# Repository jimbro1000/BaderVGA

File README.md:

# Terrible VGA #

Inspired by Ben Eater's discrete logic VGA and Leoneq's "bad vga" design,
this project implements a very basic, text only VGA display using just 1 
bit of a 128KB EEPROM data bus and 2KB of SRAM.

## Predictable issues ##

The logic chips used are clocked to near their limit (notably the 12-bit
counters) and struggle to meet the timing requirements of the design. 
Careful selection of components should help to resolve this.

The original designs by Ben and Leoneq were built on breadboard with no
practical ground plane and very little decoupling. This design is a 
dedicated 4-layer PCB with two solid ground planes that should help to 
resolve the problem. As much as possible, all signals are routed on a 
single layer with the "spare" layer used for power delivery.

Timing is not just an issue for the board's clock it is also a problem
for the host. The board clock is decoupled from the host which will,
inevitably, result in read and write conflicts. The host is expected to
be running at 3.147MHz while the video board is running at 20MHz. It
should be viable to gate host r/w operations such that they are blocked
(in the semaphore sense) by the video. If not the only option is to 
restrict write operations to the vertical blank period. The alternative
is to switch to a dual-port arrangement and bypass the problem completely.

## Integration ##
### Inputs ###

Integration with the host requires address bus, data bus, enable/select
and R/!W.

### Outputs ###

Outputs from the board, by default, are just the data bus but this needs
to be extended to include horizontal and vertical sync (TODO)

## Next ##

* Investigate dual-port ram option
* Investigate switch to 25.175MHz for better VGA compliance (can be
driven entirely from the host clock)
* Use latch and 3 bit load counter to reduce contention on databus
* Combine counter with 8 bit shift register (to reduce eeprom size
**and** allow eeprom programming on TL866 without adapters)
* Investigate combining with eeprom based state machine to manage
sync and blank timing

## References ##

Ben Eater VGA <https://eater.net/vga>

Leoneq <https://github.com/Leoneq/iNapGPU>

Dr Matt Regan VGA 
<https://github.com/Turing6502/ZX-Spectrum-No-ULA/blob/main/ZX%20Spectrum%20No%20ULA.pdf>

## License ##

This project is licensed under CC BY-SA 4.0
<https://creativecommons.org/licenses/by-sa/4.0/>

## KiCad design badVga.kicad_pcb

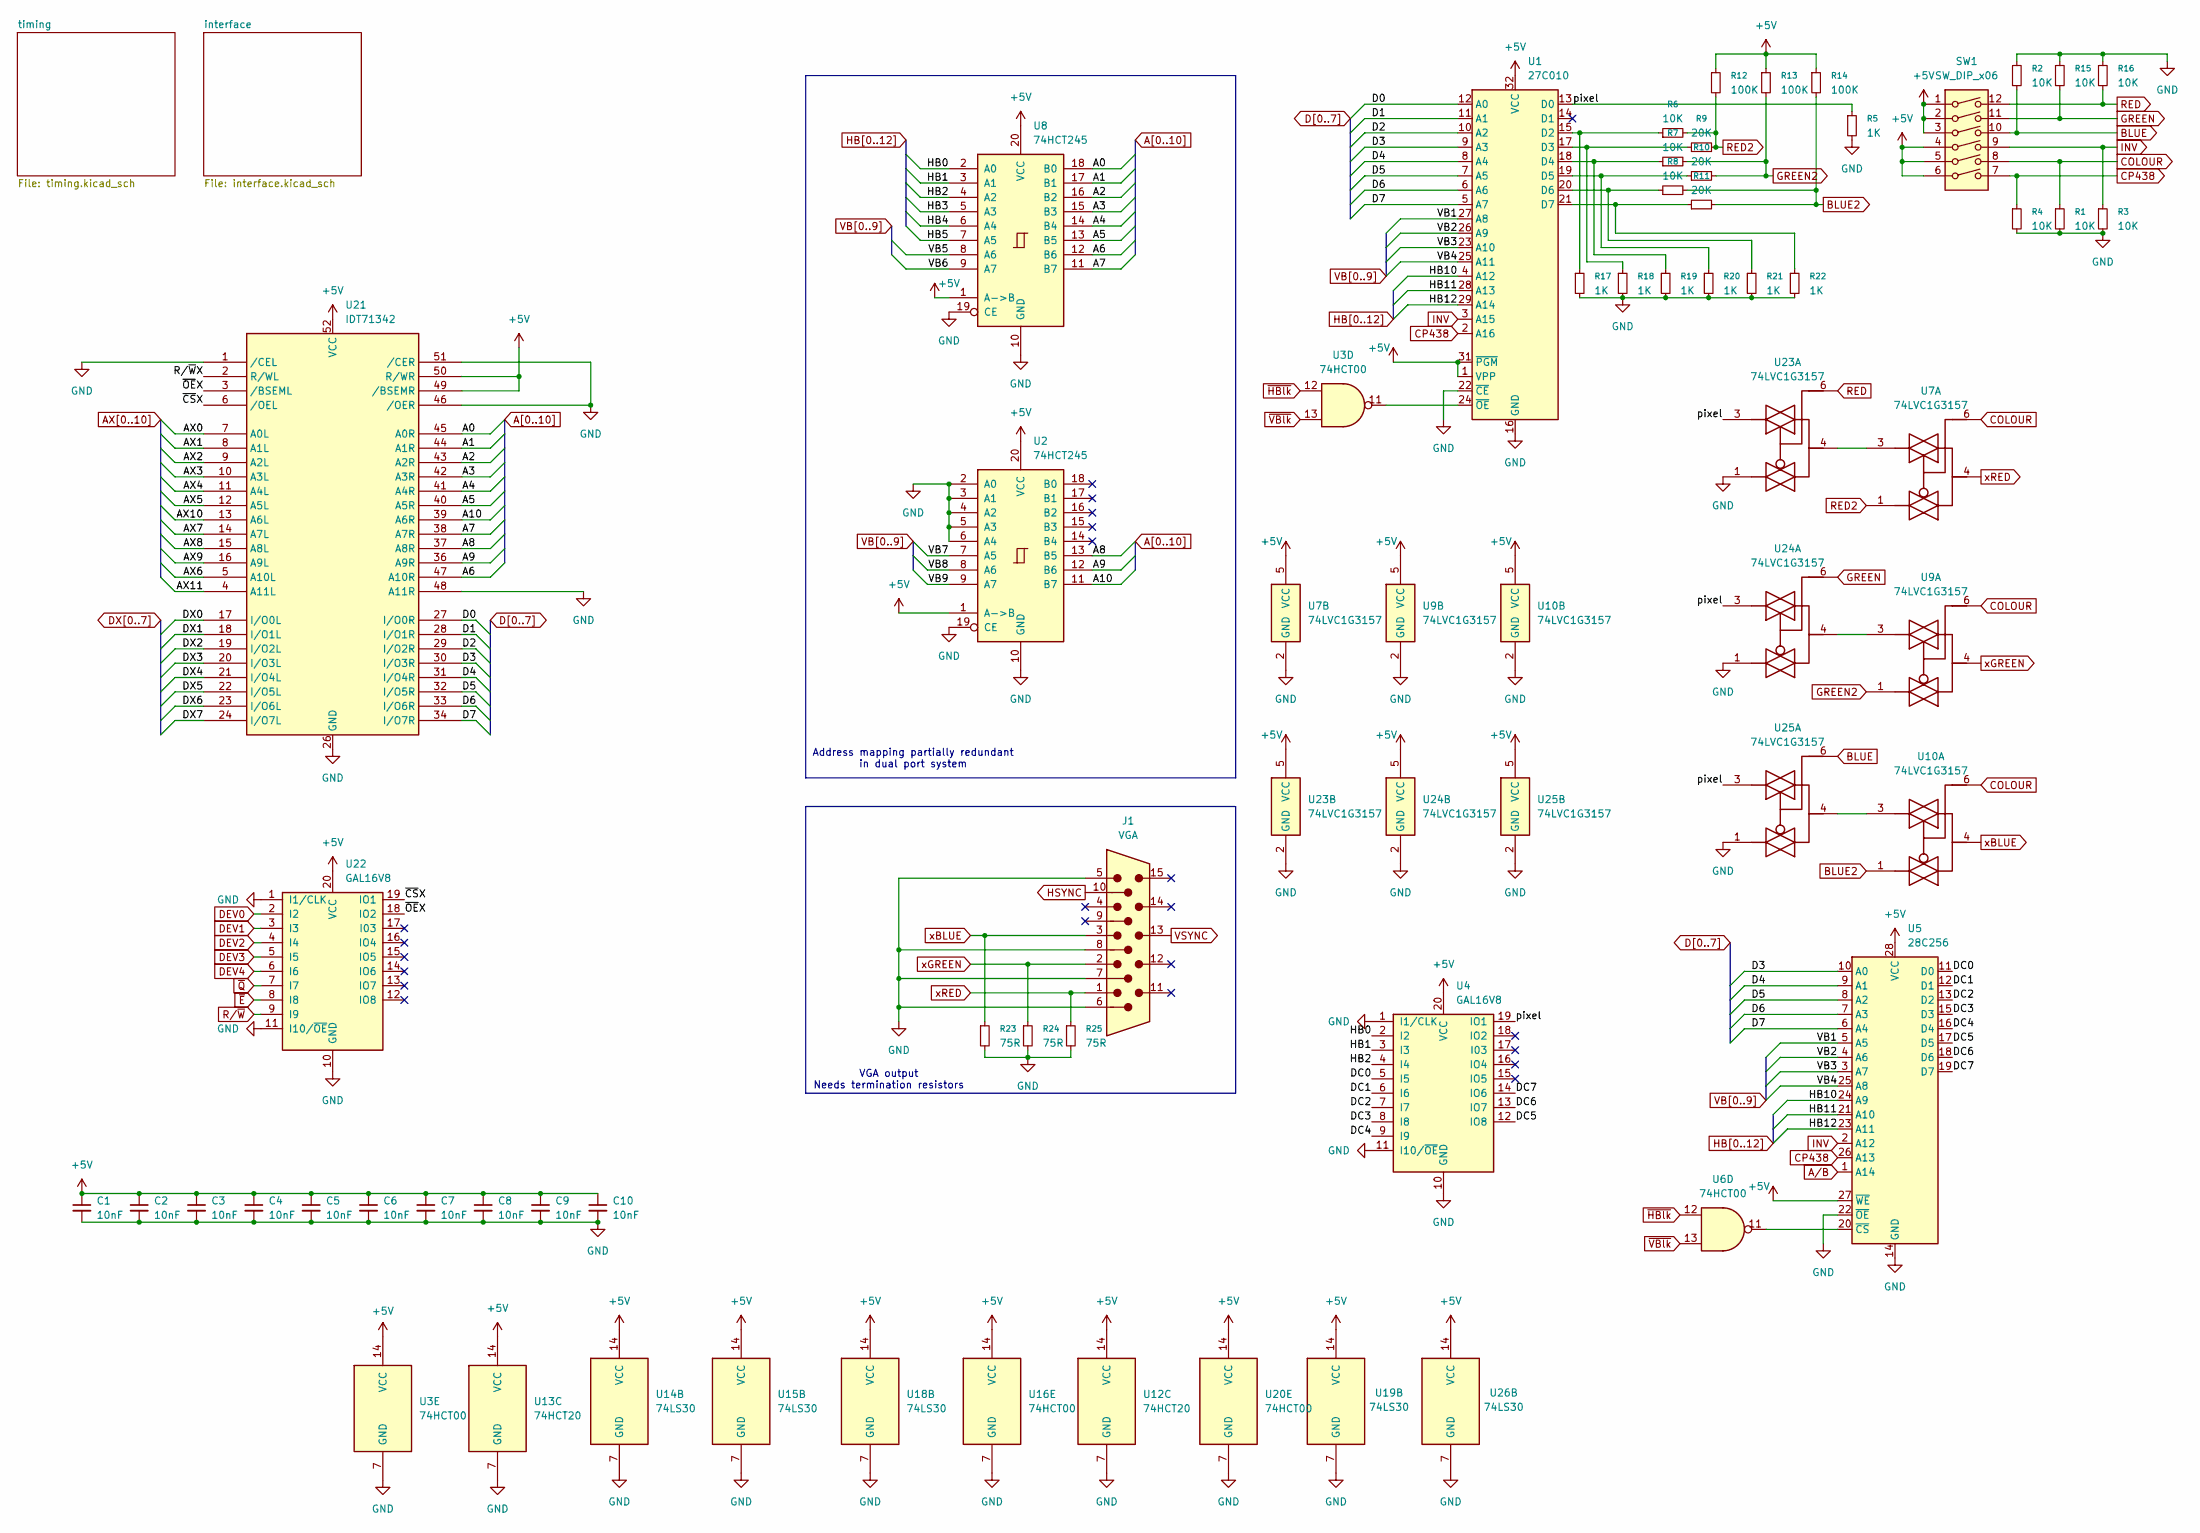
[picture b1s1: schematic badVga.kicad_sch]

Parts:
C1, C2, C3, C4, C5, C6, C7, C8, C9, C10: 10nF; C_0805_2012Metric; LCSC C1710
J1: VGA; DSUB-15-HD_Socket_Horizontal_P2.29x2.54mm_EdgePinOffset8.35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; DigiKey 123-A-HDF15A-KG-TAXB-ND
R1, R2, R3, R4, R15, R16: 10K; R_0603_1608Metric; LCSC C25804
R5, R17, R18, R19, R20, R21, R22: 1K; R_0603_1608Metric; LCSC C21190
R6, R7, R8: 10K; R_0603_1608Metric; LCSC C21190
R9, R10, R11: 20K; R_0603_1608Metric; LCSC C21190
R12, R13, R14: 100K; R_0603_1608Metric; LCSC C21190
R23, R24, R25: 75R; R_0603_1608Metric; LCSC C21190
SW1: SW_DIP_x06; SW_DIP_SPSTx06_Slide_6.7x16.8mm_W7.62mm_P2.54mm_LowProfile
U1: 27C010; DIP-32_W15.24mm
U2, U8: 74HCT245; SOIC-20W_7.5x12.8mm_P1.27mm; LCSC C2675537
U3, U16, U20: 74HCT00; SOIC-14_3.9x8.7mm_P1.27mm; LCSC C609793
U4, U22: GAL16V8; PLCC-20_THT-Socket
U5: 28C256
U6: 74HCT00; SOIC-14_3.9x8.7mm_P1.27mm
U7, U9, U10, U23, U24, U25: 74LVC1G3157; Texas_USON-6_1x1.45mm_P0.5mm_SMD; DigiKey 296-14909-1-ND
U12, U13: 74HCT20; SOIC-14_3.9x8.7mm_P1.27mm; LCSC C556253
U14, U15, U18, U19, U26: 74LS30; SOIC-14_3.9x8.7mm_P1.27mm; LCSC C547583
U21: IDT71342; PLCC-52_THT-Socket

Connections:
+5V: C1.1, C2.1, C3.1, C4.1, C5.1, C6.1, C7.1, C8.1, C9.1, C10.1, R12.1, R13.1, R14.1, SW1.1, SW1.2, SW1.3, SW1.4, SW1.5, SW1.6, U1.1 (VPP), U1.31 (~PGM), U1.32 (VCC), U2.1 (A->B), U2.20 (VCC), U3.14 (VCC), U4.20 (VCC), U5.27 (~WE), U5.28 (VCC), U7.5 (VCC), U8.1 (A->B), U8.20 (VCC), U9.5 (VCC), U10.5 (VCC), U12.14 (VCC), U13.14 (VCC), U14.14 (VCC), U15.14 (VCC), U16.14 (VCC), U18.14 (VCC), U19.14 (VCC), U20.14 (VCC), U21.49 (/BSEMR), U21.50 (R/WR), U21.52 (VCC), U22.20 (VCC), U23.5 (VCC), U24.5 (VCC), U25.5 (VCC), U26.14 (VCC); also elsewhere on the board
/AX11: U21.4 (A11L)
/R/~WX: U21.2 (R/WL)
/pixel: R5.1, U1.13 (D0), U4.19 (IO1), U23.3, U24.3, U25.3
/~CSX: U21.6 (/OEL), U22.19 (IO1)
/~OEX: U21.3 (/BSEML), U22.18 (IO2)
A0: U8.18 (B0), U21.45 (A0R)
A1: U8.17 (B1), U21.44 (A1R)
A2: U8.16 (B2), U21.43 (A2R)
A3: U8.15 (B3), U21.42 (A3R)
A4: U8.14 (B4), U21.41 (A4R)
A5: U8.13 (B5), U21.40 (A5R)
A6: U8.12 (B6), U21.47 (A10R)
A7: U8.11 (B7), U21.38 (A7R)
A8: U2.13 (B5), U21.37 (A8R)
A9: U2.12 (B6), U21.36 (A9R)
A10: U2.11 (B7), U21.39 (A6R)
AX0: U21.7 (A0L); also elsewhere on the board
AX1: U21.8 (A1L); also elsewhere on the board
AX2: U21.9 (A2L); also elsewhere on the board
AX3: U21.10 (A3L); also elsewhere on the board
AX4: U21.11 (A4L); also elsewhere on the board
AX5: U21.12 (A5L); also elsewhere on the board
AX6: U21.5 (A10L); also elsewhere on the board
AX7: U21.14 (A7L); also elsewhere on the board
AX8: U21.15 (A8L); also elsewhere on the board
AX9: U21.16 (A9L); also elsewhere on the board
AX10: U21.13 (A6L); also elsewhere on the board
BLUE: R2.2, SW1.10, U25.6
BLUE2: R8.2, R11.2, R14.2, U10.1
COLOUR: R1.1, SW1.8, U7.6, U9.6, U10.6
CP438: R4.1, SW1.7, U1.2 (A16), U5.26 (A13)
D0: U1.12 (A0), U21.27 (I/O0R)
D1: U1.11 (A1), U21.28 (I/O1R)
D2: U1.10 (A2), U21.29 (I/O2R)
D3: U1.9 (A3), U5.10 (A0), U21.30 (I/O3R)
D4: U1.8 (A4), U5.9 (A1), U21.31 (I/O4R)
D5: U1.7 (A5), U5.8 (A2), U21.32 (I/O5R)
D6: U1.6 (A6), U5.7 (A3), U21.33 (I/O6R)
D7: U1.5 (A7), U5.6 (A4), U21.34 (I/O7R)
DEV0: U22.2 (I2); also elsewhere on the board
DEV1: U22.3 (I3); also elsewhere on the board
DEV2: U22.4 (I4); also elsewhere on the board
DEV3: U22.5 (I5); also elsewhere on the board
DEV4: U22.6 (I6); also elsewhere on the board
DX0: U21.17 (I/O0L); also elsewhere on the board
DX1: U21.18 (I/O1L); also elsewhere on the board
DX2: U21.19 (I/O2L); also elsewhere on the board
DX3: U21.20 (I/O3L); also elsewhere on the board
DX4: U21.21 (I/O4L); also elsewhere on the board
DX5: U21.22 (I/O5L); also elsewhere on the board
DX6: U21.23 (I/O6L); also elsewhere on the board
DX7: U21.24 (I/O7L); also elsewhere on the board
GND: C1.2, C2.2, C3.2, C4.2, C5.2, C6.2, C7.2, C8.2, C9.2, C10.2, J1.5, J1.6, J1.7, J1.8, R1.2, R2.1, R3.2, R4.2, R5.2, R15.1, R16.1, R17.2, R18.2, R19.2, R20.2, R21.2, R22.2, R23.2, R24.2, R25.2, U1.16 (GND), U1.22 (~CE), U2.2 (A0), U2.3 (A1), U2.4 (A2), U2.5 (A3), U2.6 (A4), U2.10 (GND), U2.19 (CE), U3.7 (GND), U4.1 (I1/CLK), U4.10 (GND), U4.11 (I10/~OE), U5.14 (GND), U5.22 (~OE), U7.2 (GND), U8.10 (GND), U8.19 (CE), U9.2 (GND), U10.2 (GND), U12.7 (GND), U13.7 (GND), U14.7 (GND), U15.7 (GND), U16.7 (GND), U18.7 (GND), U19.7 (GND), U20.7 (GND), U21.1 (/CEL), U21.26 (GND), U21.46 (/OER), U21.48 (A11R), U21.51 (/CER), U22.1 (I1/CLK), U22.10 (GND), U22.11 (I10/~OE), U23.1, U23.2 (GND), U24.1, U24.2 (GND), U25.1, U25.2 (GND), U26.7 (GND); also elsewhere on the board
GREEN: R15.2, SW1.11, U24.6
GREEN2: R7.2, R10.2, R13.2, U9.1
HB0: U4.2 (I2), U8.2 (A0); also elsewhere on the board
HB1: U4.3 (I3), U8.3 (A1); also elsewhere on the board
HB2: U4.4 (I4), U8.4 (A2); also elsewhere on the board
HB3: U8.5 (A3); also elsewhere on the board
HB4: U8.6 (A4); also elsewhere on the board
HB5: U8.7 (A5); also elsewhere on the board
HB10: U1.4 (A12), U5.24 (A9); also elsewhere on the board
HB11: U1.28 (A13), U5.21 (A10); also elsewhere on the board
HB12: U1.29 (A14), U5.23 (A11); also elsewhere on the board
HSYNC: J1.10; also elsewhere on the board
INV: R3.1, SW1.9, U1.3 (A15), U5.2 (A12)
unnamed: R6.1, R17.1, U1.15 (D2)
unnamed: R9.1, R18.1, U1.17 (D3)
unnamed: R7.1, R19.1, U1.18 (D4)
unnamed: R10.1, R20.1, U1.19 (D5)
unnamed: R8.1, R21.1, U1.20 (D6)
unnamed: R11.1, R22.1, U1.21 (D7)
unnamed: U1.24 (~OE), U3.11
unnamed: U4.5 (I5), U5.11 (D0)
unnamed: U4.6 (I6), U5.12 (D1)
unnamed: U4.7 (I7), U5.13 (D2)
unnamed: U4.8 (I8), U5.15 (D3)
unnamed: U4.9 (I9), U5.16 (D4)
unnamed: U4.12 (IO8), U5.17 (D5)
unnamed: U4.13 (IO7), U5.18 (D6)
unnamed: U4.14 (IO6), U5.19 (D7)
unnamed: U5.20 (~CS), U6.11
unnamed: U10.3, U25.4
unnamed: U7.3, U23.4
unnamed: U9.3, U24.4
RED: R16.2, SW1.12, U23.6
RED2: R6.2, R9.2, R12.2, U7.1
R/~W: U22.9 (I9); also elsewhere on the board
VB1: U1.27 (A8), U5.5 (A5); also elsewhere on the board
VB2: U1.26 (A9), U5.4 (A6); also elsewhere on the board
VB3: U1.23 (A10), U5.3 (A7); also elsewhere on the board
VB4: U1.25 (A11), U5.25 (A8); also elsewhere on the board
VB5: U8.8 (A6); also elsewhere on the board
VB6: U8.9 (A7); also elsewhere on the board
VB7: U2.7 (A5); also elsewhere on the board
VB8: U2.8 (A6); also elsewhere on the board
VB9: U2.9 (A7); also elsewhere on the board
VSYNC: J1.13; also elsewhere on the board
xBLUE: J1.3, R23.1, U10.4
xGREEN: J1.2, R24.1, U9.4
xRED: J1.1, R25.1, U7.4
~E: U22.8 (I8); also elsewhere on the board
~HBlk: U3.12, U6.12; also elsewhere on the board
~Q: U22.7 (I7); also elsewhere on the board
~VBlk: U3.13, U6.13; also elsewhere on the board

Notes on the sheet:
Address mapping partially redundant in dual port system
VGA output Needs termination resistors

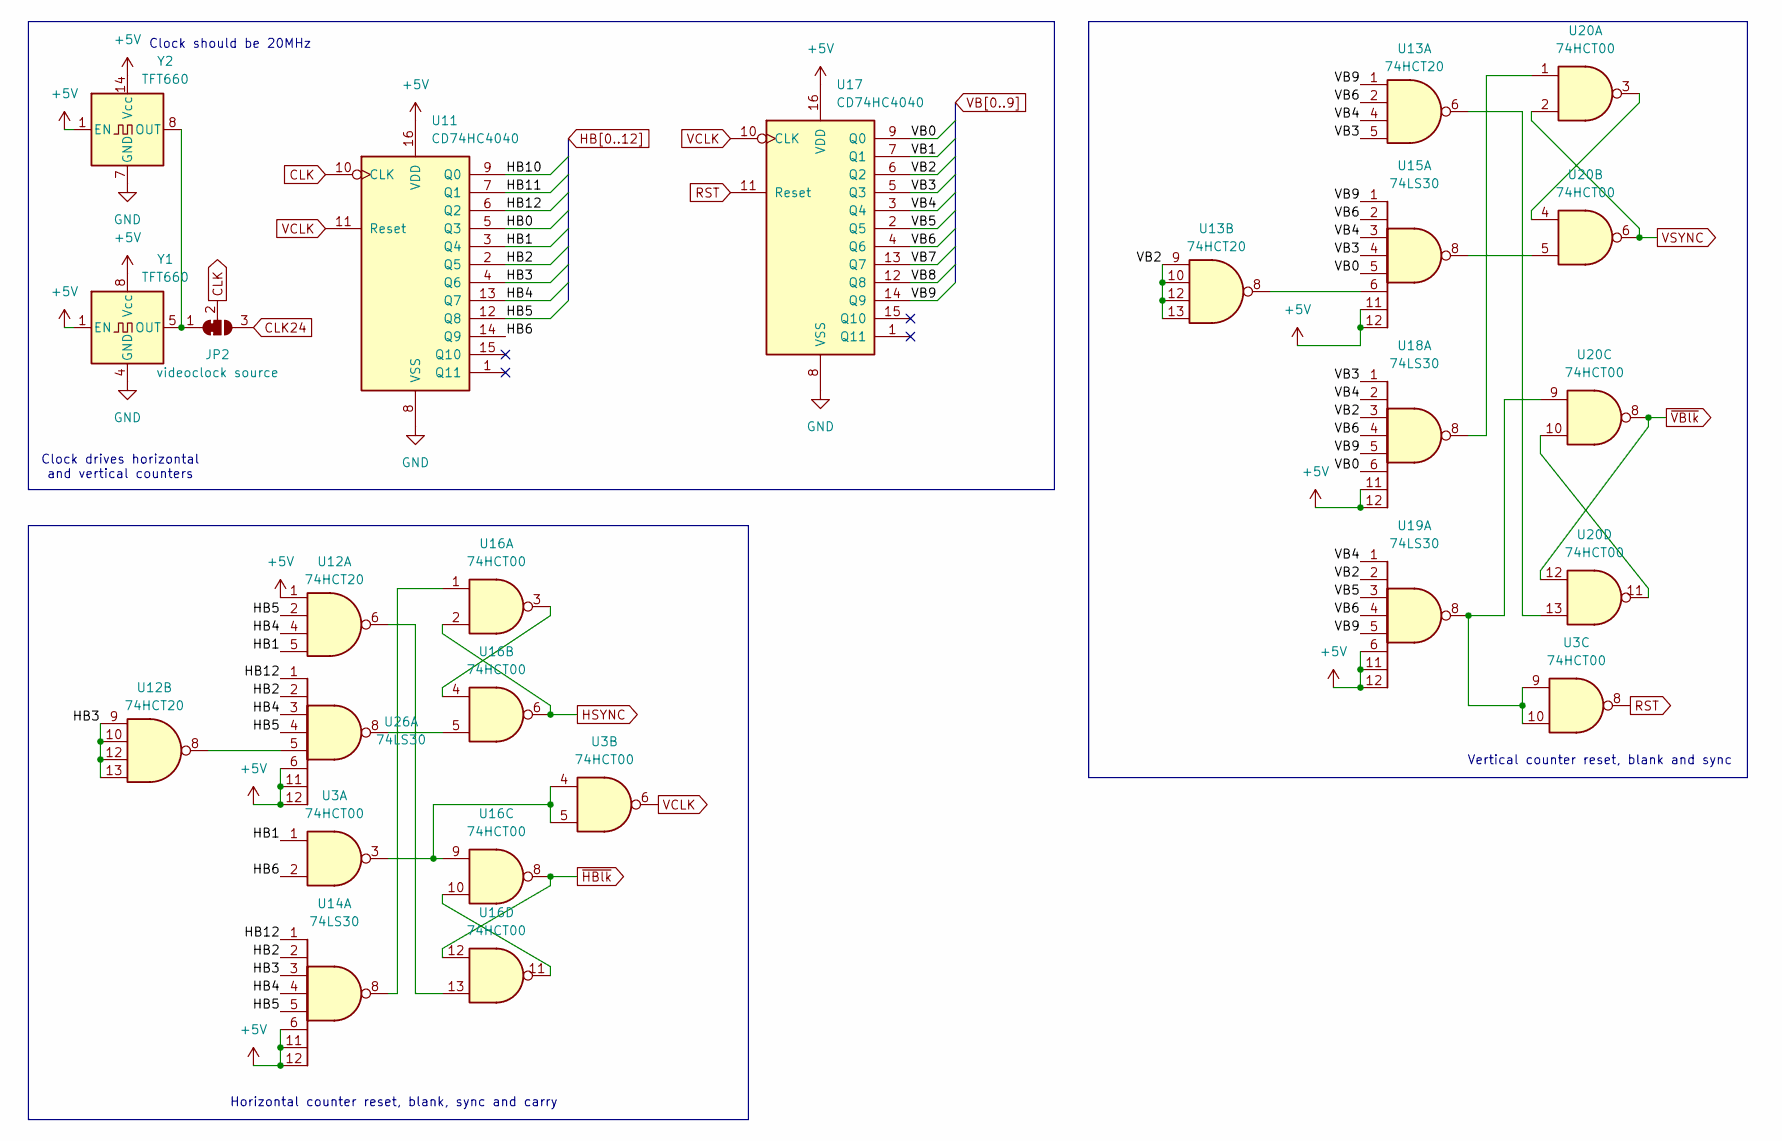
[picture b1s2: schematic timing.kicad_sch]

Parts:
JP2: videoclock source; SolderJumper-3_P1.3mm_Bridged12_Pad1.0x1.5mm
U3, U16, U20: 74HCT00; SOIC-14_3.9x8.7mm_P1.27mm; LCSC C609793
U11, U17: CD74HC4040; SOIC-16_3.9x9.9mm_P1.27mm; LCSC C2865249
U12, U13: 74HCT20; SOIC-14_3.9x8.7mm_P1.27mm; LCSC C556253
U14, U15, U18, U19, U26: 74LS30; SOIC-14_3.9x8.7mm_P1.27mm; LCSC C547583
Y1: TFT660; Oscillator_DIP-8
Y2: TFT660; Oscillator_DIP-14

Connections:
+5V: U11.16 (VDD), U12.1, U14.6, U14.11, U14.12, U15.11, U15.12, U17.16 (VDD), U18.11, U18.12, U19.6, U19.11, U19.12, U26.6, U26.11, U26.12, Y1.1 (EN), Y1.8 (Vcc), Y2.1 (EN), Y2.14 (Vcc); also elsewhere on the board
CLK: JP2.2 (C), U11.10 (CLK)
CLK24: JP2.3 (B); also elsewhere on the board
GND: U11.8 (VSS), U17.8 (VSS), Y1.4 (GND), Y2.7 (GND); also elsewhere on the board
HB0: U11.5 (Q3); also elsewhere on the board
HB1: U3.1, U11.3 (Q4), U12.5; also elsewhere on the board
HB2: U11.2 (Q5), U14.2, U26.2; also elsewhere on the board
HB3: U11.4 (Q6), U12.9, U12.10, U12.12, U12.13, U14.3; also elsewhere on the board
HB4: U11.13 (Q7), U12.4, U14.4, U26.3; also elsewhere on the board
HB5: U11.12 (Q8), U12.2, U14.5, U26.4; also elsewhere on the board
HB6: U3.2, U11.14 (Q9)
HB10: U11.9 (Q0); also elsewhere on the board
HB11: U11.7 (Q1); also elsewhere on the board
HB12: U11.6 (Q2), U14.1, U26.1; also elsewhere on the board
HSYNC: U16.2, U16.6; also elsewhere on the board
unnamed: JP2.1 (A), Y1.5 (OUT), Y2.8 (OUT)
unnamed: U12.6, U16.13
unnamed: U12.8, U26.5
unnamed: U13.6, U20.13
unnamed: U13.8, U15.6
unnamed: U14.8, U16.1
unnamed: U15.8, U20.5
unnamed: U16.3, U16.4
unnamed: U16.5, U26.8
unnamed: U3.3, U3.4, U3.5, U16.9
unnamed: U16.10, U16.11
unnamed: U18.8, U20.1
unnamed: U3.9, U3.10, U19.8, U20.9
unnamed: U20.3, U20.4
unnamed: U20.10, U20.11
RST: U3.8, U17.11 (Reset)
VB0: U15.5, U17.9 (Q0), U18.6
VB1: U17.7 (Q1); also elsewhere on the board
VB2: U13.9, U13.10, U13.12, U13.13, U17.6 (Q2), U18.3, U19.2; also elsewhere on the board
VB3: U13.5, U15.4, U17.5 (Q3), U18.1; also elsewhere on the board
VB4: U13.4, U15.3, U17.3 (Q4), U18.2, U19.1; also elsewhere on the board
VB5: U17.2 (Q5), U19.3; also elsewhere on the board
VB6: U13.2, U15.2, U17.4 (Q6), U18.4, U19.4; also elsewhere on the board
VB7: U17.13 (Q7); also elsewhere on the board
VB8: U17.12 (Q8); also elsewhere on the board
VB9: U13.1, U15.1, U17.14 (Q9), U18.5, U19.5; also elsewhere on the board
VCLK: U3.6, U11.11 (Reset), U17.10 (CLK)
VSYNC: U20.2, U20.6; also elsewhere on the board
~HBlk: U16.8, U16.12; also elsewhere on the board
~VBlk: U20.8, U20.12; also elsewhere on the board

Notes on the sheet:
Clock should be 20MHz
Vertical counter reset, blank and sync
Clock drives horizontal and vertical counters
Horizontal counter reset, blank, sync and carry

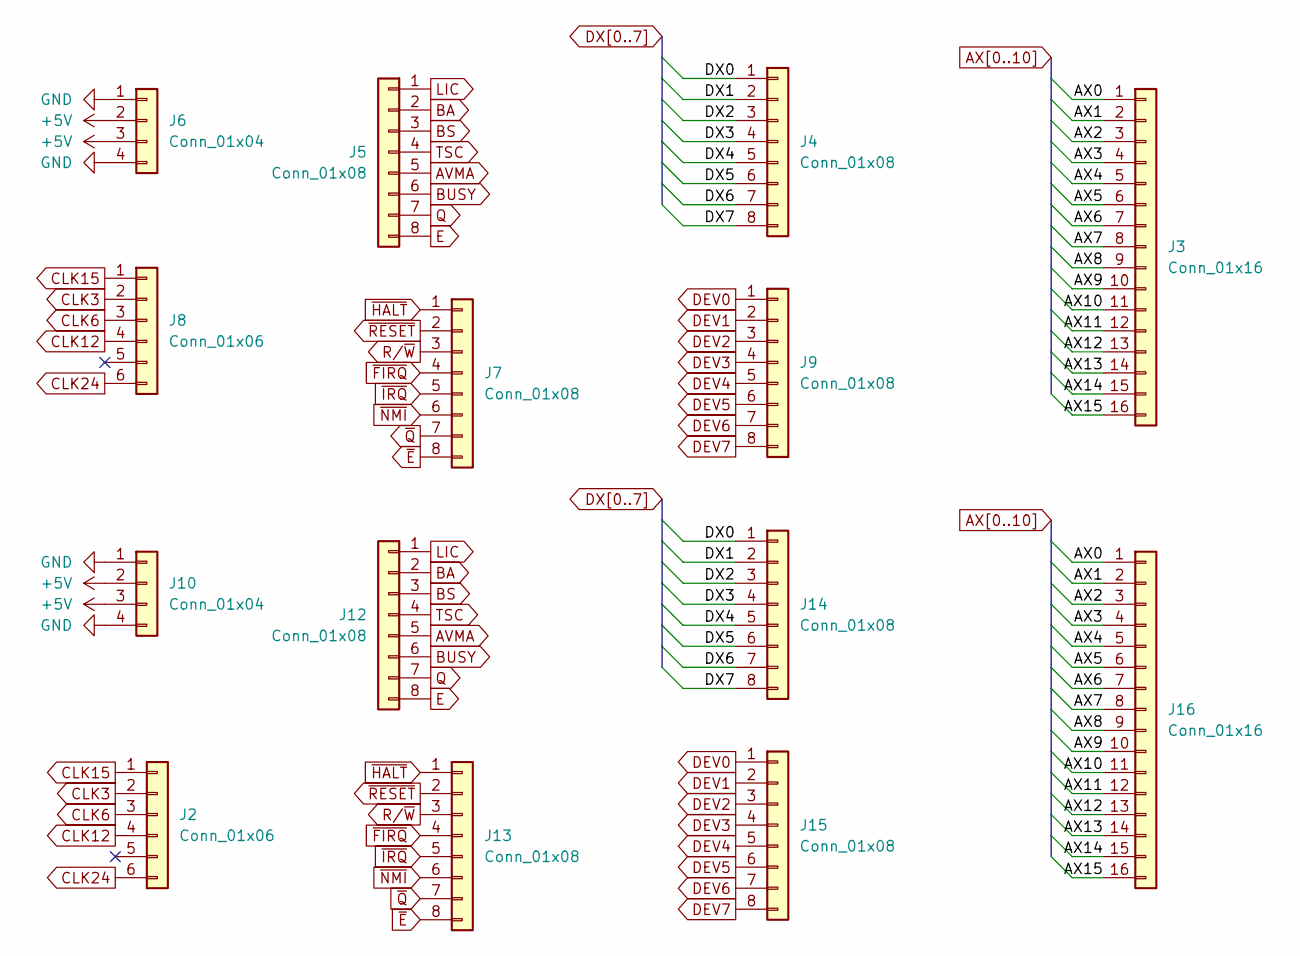
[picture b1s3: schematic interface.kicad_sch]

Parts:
J2, J8: Conn_01x06; PinHeader_1x06_P2.54mm_Vertical
J3, J16: Conn_01x16; PinHeader_1x16_P2.54mm_Vertical
J4, J5, J7, J9, J12, J13, J14, J15: Conn_01x08; PinHeader_1x08_P2.54mm_Vertical
J6, J10: Conn_01x04; PinHeader_1x04_P2.54mm_Vertical

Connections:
+5V: J6.2, J6.3, J10.2, J10.3; also elsewhere on the board
/interface/AX11: J3.12, J16.12
/interface/AX12: J3.13, J16.13
/interface/AX13: J3.14, J16.14
/interface/AX14: J3.15, J16.15
/interface/AX15: J3.16, J16.16
AVMA: J5.5, J12.5
AX0: J3.1, J16.1; also elsewhere on the board
AX1: J3.2, J16.2; also elsewhere on the board
AX2: J3.3, J16.3; also elsewhere on the board
AX3: J3.4, J16.4; also elsewhere on the board
AX4: J3.5, J16.5; also elsewhere on the board
AX5: J3.6, J16.6; also elsewhere on the board
AX6: J3.7, J16.7; also elsewhere on the board
AX7: J3.8, J16.8; also elsewhere on the board
AX8: J3.9, J16.9; also elsewhere on the board
AX9: J3.10, J16.10; also elsewhere on the board
AX10: J3.11, J16.11; also elsewhere on the board
BA: J5.2, J12.2
BS: J5.3, J12.3
BUSY: J5.6, J12.6
CLK3: J2.2, J8.2
CLK6: J2.3, J8.3
CLK12: J2.4, J8.4
CLK15: J2.1, J8.1
CLK24: J2.6, J8.6; also elsewhere on the board
DEV0: J9.1, J15.1; also elsewhere on the board
DEV1: J9.2, J15.2; also elsewhere on the board
DEV2: J9.3, J15.3; also elsewhere on the board
DEV3: J9.4, J15.4; also elsewhere on the board
DEV4: J9.5, J15.5; also elsewhere on the board
DEV5: J9.6, J15.6
DEV6: J9.7, J15.7
DEV7: J9.8, J15.8
DX0: J4.1, J14.1; also elsewhere on the board
DX1: J4.2, J14.2; also elsewhere on the board
DX2: J4.3, J14.3; also elsewhere on the board
DX3: J4.4, J14.4; also elsewhere on the board
DX4: J4.5, J14.5; also elsewhere on the board
DX5: J4.6, J14.6; also elsewhere on the board
DX6: J4.7, J14.7; also elsewhere on the board
DX7: J4.8, J14.8; also elsewhere on the board
E: J5.8, J12.8
GND: J6.1, J6.4, J10.1, J10.4; also elsewhere on the board
LIC: J5.1, J12.1
Q: J5.7, J12.7
R/~W: J7.3, J13.3; also elsewhere on the board
TSC: J5.4, J12.4
~E: J7.8, J13.8; also elsewhere on the board
~FIRQ: J7.4, J13.4
~HALT: J7.1, J13.1
~IRQ: J7.5, J13.5
~NMI: J7.6, J13.6
~Q: J7.7, J13.7; also elsewhere on the board
~RESET: J7.2, J13.2

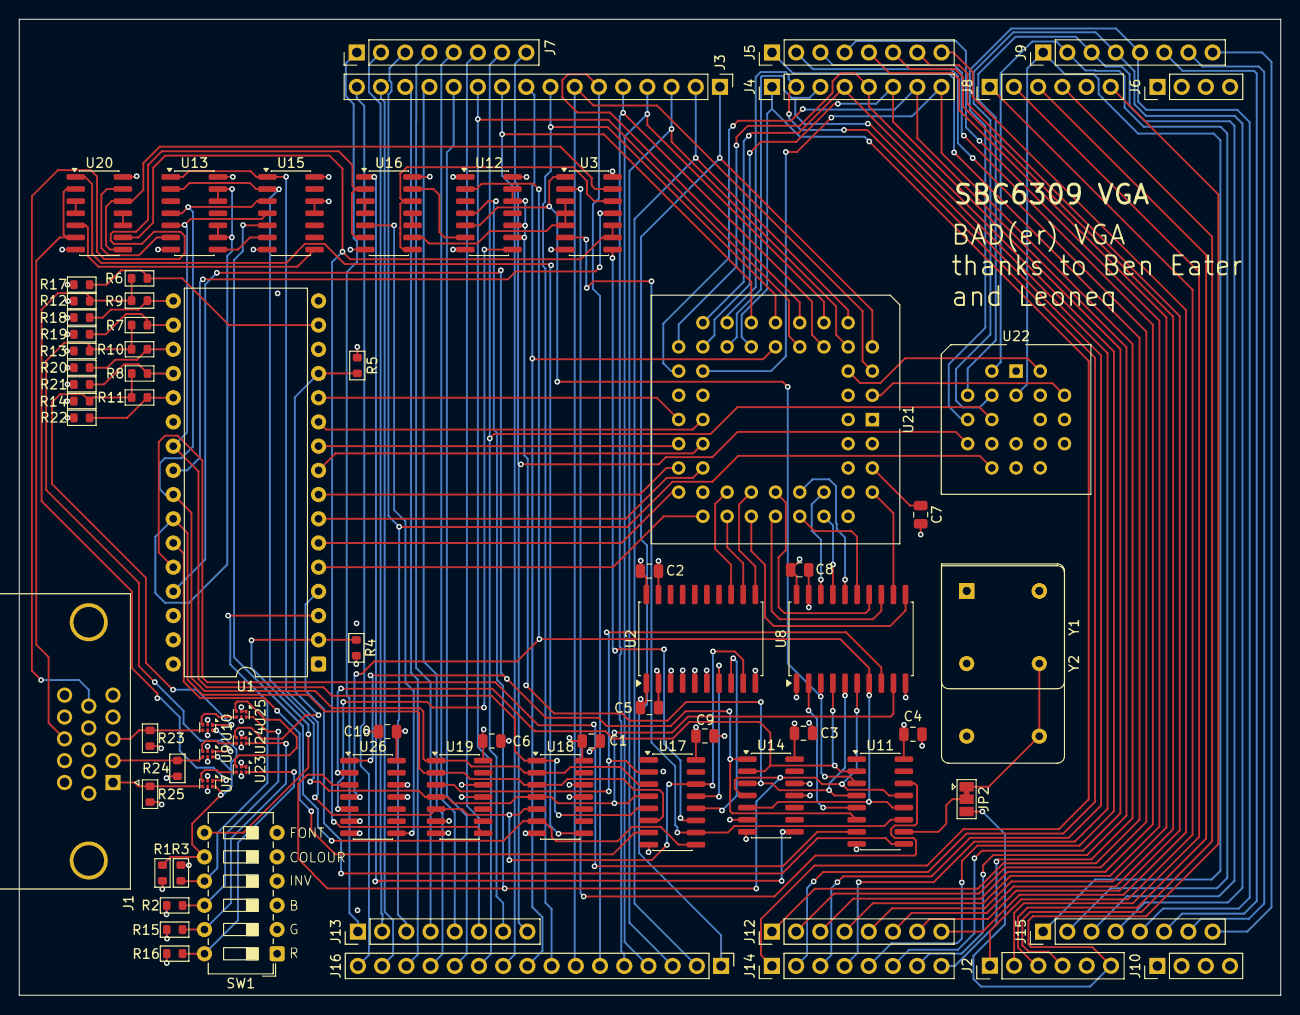
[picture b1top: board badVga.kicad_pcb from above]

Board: 4 copper layers, 132.3 x 102.4 mm, 77 parts (0 on the bottom side), 141 nets.

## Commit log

2025-11-22 adjust to sbc6309 io
2026-01-30 improve rom use
2026-01-30 add GAL code
2026-01-31 fix sync signal generation
2026-01-31 fix sync signals
